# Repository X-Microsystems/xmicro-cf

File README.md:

# XMICRO-CF

[XMICRO](https://github.com/x-microsystems/xmicro-bus) card providing a CompactFlash card interface and real-time
clock.

Datasheet: [XMICRO-CF](Documentation/XMICRO-CF.pdf)

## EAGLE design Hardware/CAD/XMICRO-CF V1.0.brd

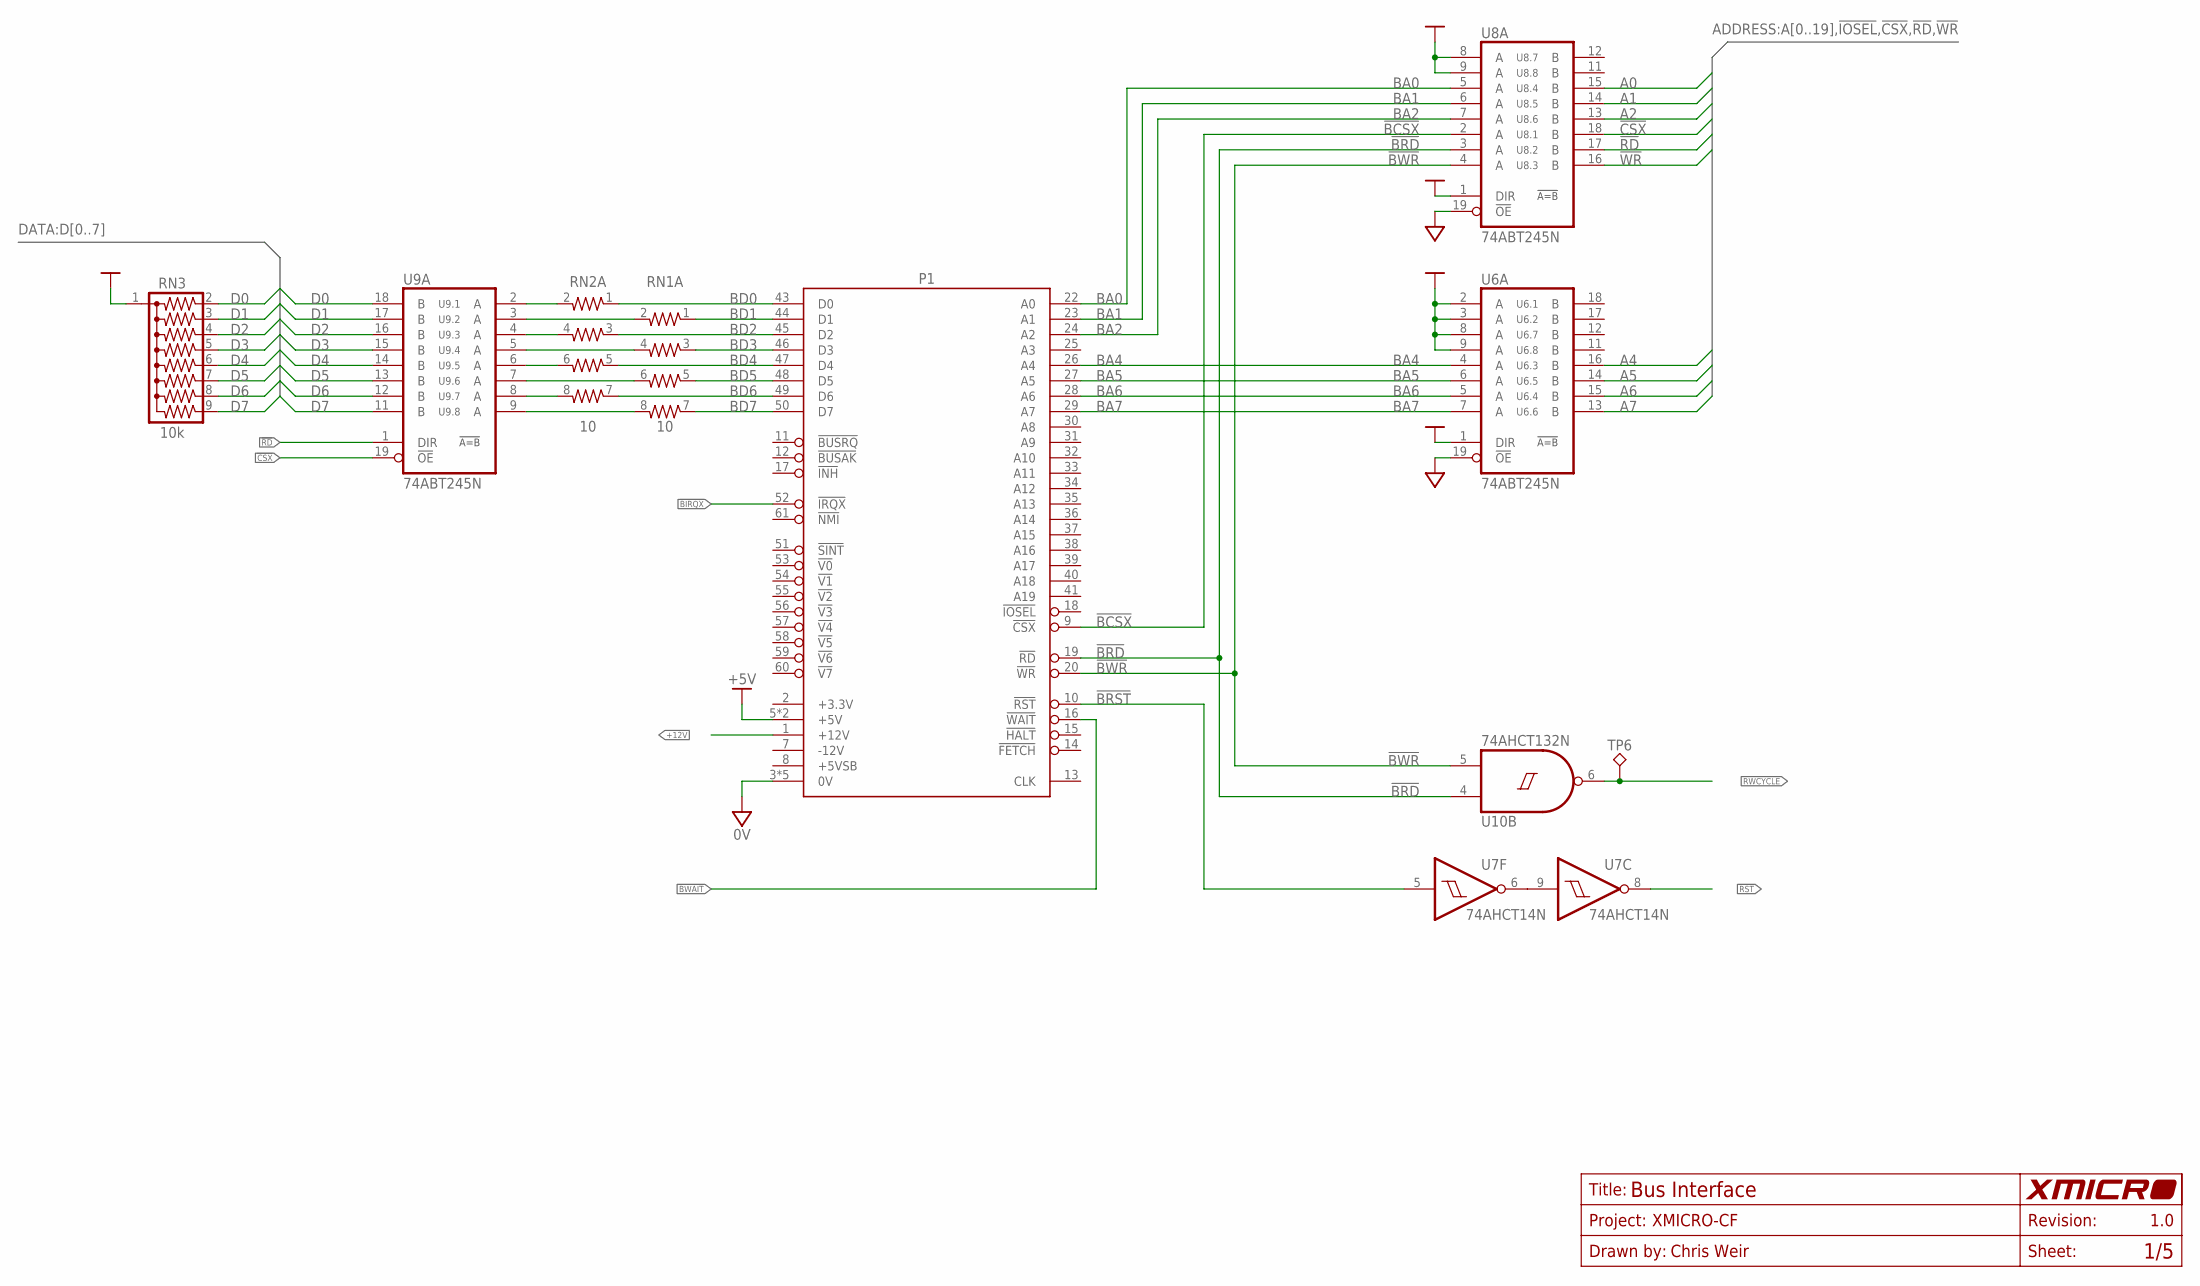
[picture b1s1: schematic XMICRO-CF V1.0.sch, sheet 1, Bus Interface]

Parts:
P1: XMICRO-BUS-EDGE; EDGE62M
RN1, RN2: 10; SIL8
RN3: 10k; SIL9
TP6: TP-040
U6, U8, U9: 74ABT245N; DIL20
U7: 74AHCT14N; DIL14
U10: 74AHCT132N; DIL14

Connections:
0V: P1.3 (0V), P1.4 (0V), P1.21 (0V), P1.42 (0V), P1.62 (0V), U6.10 (0V), U6.19 (!OE), U7.7 (0V), U8.10 (0V), U8.19 (!OE), U9.10 (0V), U10.7 (0V); also elsewhere on the board
!BCSX: P1.9 (!CSX), U8.2 (A)
!BIRQX: P1.52 (!IRQX); also elsewhere on the board
!BRD: P1.19 (!RD), U8.3 (A), U10.4 (I0)
!BRST: P1.10 (!RST), U7.5 (I)
!BWAIT: P1.16 (!WAIT); also elsewhere on the board
!BWR: P1.20 (!WR), U8.4 (A), U10.5 (I1)
!CSX: U8.18 (B), U9.19 (!OE); also elsewhere on the board
!RD: U8.17 (B), U9.1 (DIR); also elsewhere on the board
!RST: U7.8 (O); also elsewhere on the board
!WR: U8.16 (B); also elsewhere on the board
+5V: P1.5 (+5V), P1.6 (+5V), RN3.1, U6.1 (DIR), U6.2 (A), U6.3 (A), U6.8 (A), U6.9 (A), U6.20 (+5V), U7.14 (+5V), U8.1 (DIR), U8.8 (A), U8.9 (A), U8.20 (+5V), U9.20 (+5V), U10.14 (+5V); also elsewhere on the board
+12V: P1.1 (+12V); also elsewhere on the board
A0: U8.15 (B); also elsewhere on the board
A1: U8.14 (B); also elsewhere on the board
A2: U8.13 (B); also elsewhere on the board
A4: U6.16 (B); also elsewhere on the board
A5: U6.14 (B); also elsewhere on the board
A6: U6.15 (B); also elsewhere on the board
A7: U6.13 (B); also elsewhere on the board
BA0: P1.22 (A0), U8.5 (A)
BA1: P1.23 (A1), U8.6 (A)
BA2: P1.24 (A2), U8.7 (A)
BA4: P1.26 (A4), U6.4 (A)
BA5: P1.27 (A5), U6.6 (A)
BA6: P1.28 (A6), U6.5 (A)
BA7: P1.29 (A7), U6.7 (A)
BD0: P1.43 (D0), RN2.1
BD1: P1.44 (D1), RN1.1
BD2: P1.45 (D2), RN2.3 (1)
BD3: P1.46 (D3), RN1.3 (1)
BD4: P1.47 (D4), RN2.5 (1)
BD5: P1.48 (D5), RN1.5 (1)
BD6: P1.49 (D6), RN2.7 (1)
BD7: P1.50 (D7), RN1.7 (1)
D0: RN3.2, U9.18 (B); also elsewhere on the board
D1: RN3.3, U9.17 (B); also elsewhere on the board
D2: RN3.4, U9.16 (B); also elsewhere on the board
D3: RN3.5, U9.15 (B); also elsewhere on the board
D4: RN3.6, U9.14 (B); also elsewhere on the board
D5: RN3.7, U9.13 (B); also elsewhere on the board
D6: RN3.8, U9.12 (B); also elsewhere on the board
D7: RN3.9, U9.11 (B); also elsewhere on the board
unnamed: U7.6 (O), U7.9 (I)
unnamed: RN2.2, U9.2 (A)
unnamed: RN1.2, U9.3 (A)
unnamed: RN2.4 (2), U9.4 (A)
unnamed: RN1.4 (2), U9.5 (A)
unnamed: RN2.6 (2), U9.6 (A)
unnamed: RN1.6 (2), U9.7 (A)
unnamed: RN2.8 (2), U9.8 (A)
unnamed: RN1.8 (2), U9.9 (A)
RWCYCLE: TP6.1, U10.6 (O); also elsewhere on the board

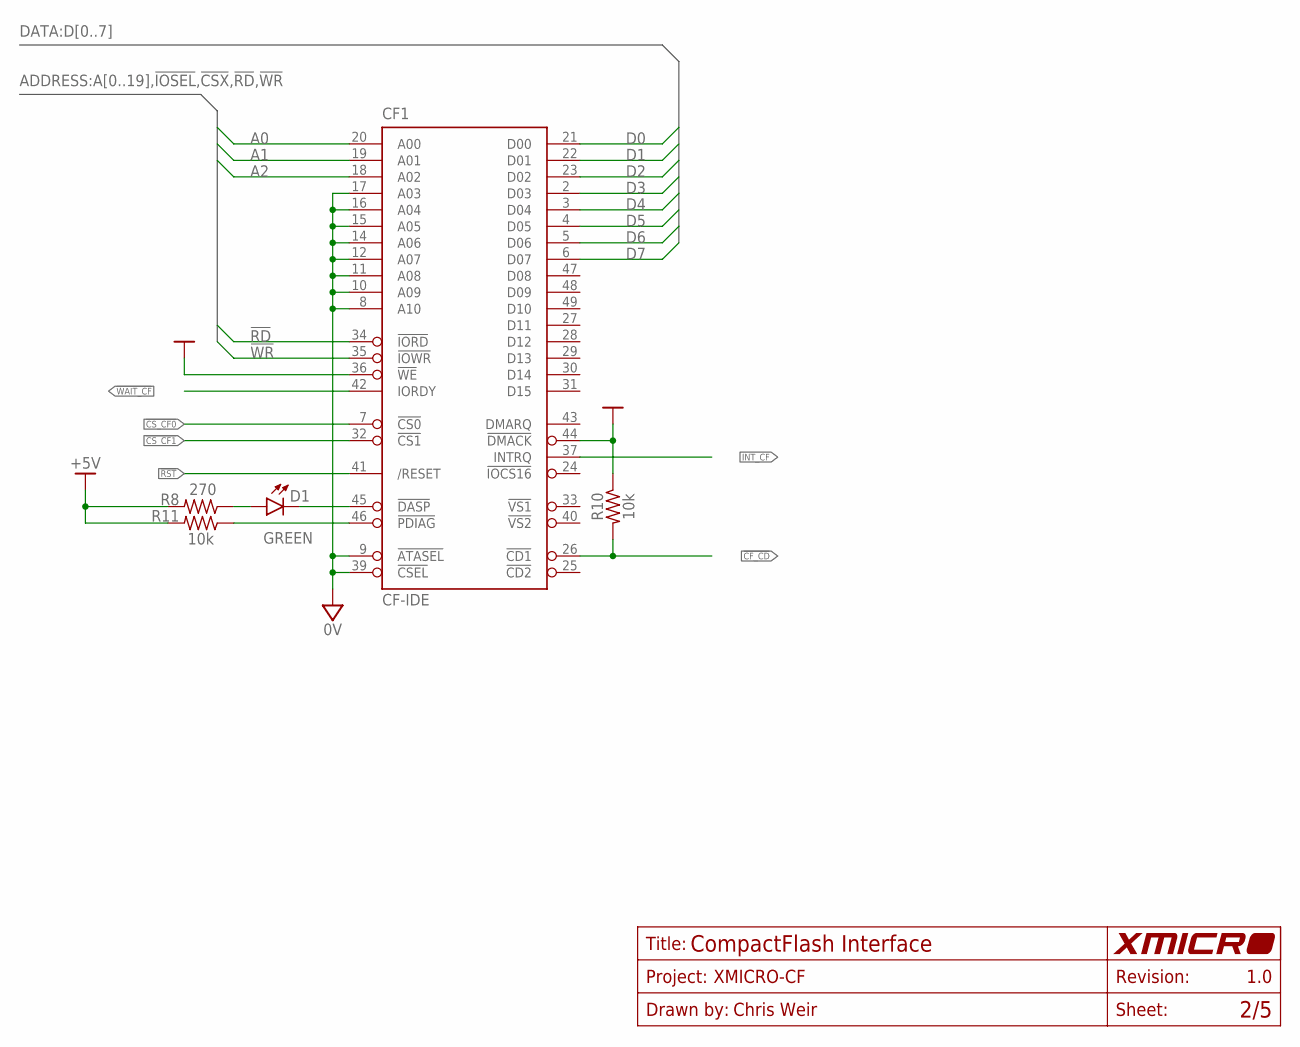
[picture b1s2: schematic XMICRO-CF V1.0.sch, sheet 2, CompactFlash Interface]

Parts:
CF1: CF-IDE; CF-KYOCERA
D1: GREEN; LED-3R
R8: 270; 0207/10
R10, R11: 10k; 0207/10

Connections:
0V: CF1.1 (0V), CF1.8 (A10), CF1.9 (!ATASEL), CF1.10 (A09), CF1.11 (A08), CF1.12 (A07), CF1.14 (A06), CF1.15 (A05), CF1.16 (A04), CF1.17 (A03), CF1.39 (!CSEL), CF1.50 (0V), CF1.M1 (0V), CF1.M2 (0V); also elsewhere on the board
!CF_CD: CF1.26 (!CD1), R10.2; also elsewhere on the board
!CS_CF0: CF1.7 (!CS0); also elsewhere on the board
!CS_CF1: CF1.32 (!CS1); also elsewhere on the board
!RD: CF1.34 (!IORD); also elsewhere on the board
!RST: CF1.41 (/RESET); also elsewhere on the board
!WAIT_CF: CF1.42 (IORDY); also elsewhere on the board
!WR: CF1.35 (!IOWR); also elsewhere on the board
+5V: CF1.13 (+5V), CF1.36 (!WE), CF1.38 (+5V), CF1.44 (!DMACK), R8.2, R10.1, R11.2; also elsewhere on the board
A0: CF1.20 (A00); also elsewhere on the board
A1: CF1.19 (A01); also elsewhere on the board
A2: CF1.18 (A02); also elsewhere on the board
D0: CF1.21 (D00); also elsewhere on the board
D1: CF1.22 (D01); also elsewhere on the board
D2: CF1.23 (D02); also elsewhere on the board
D3: CF1.2 (D03); also elsewhere on the board
D4: CF1.3 (D04); also elsewhere on the board
D5: CF1.4 (D05); also elsewhere on the board
D6: CF1.5 (D06); also elsewhere on the board
D7: CF1.6 (D07); also elsewhere on the board
INT_CF: CF1.37 (INTRQ); also elsewhere on the board
unnamed: CF1.45 (!DASP), D1.C
unnamed: D1.A, R8.1
unnamed: CF1.46 (!PDIAG), R11.1

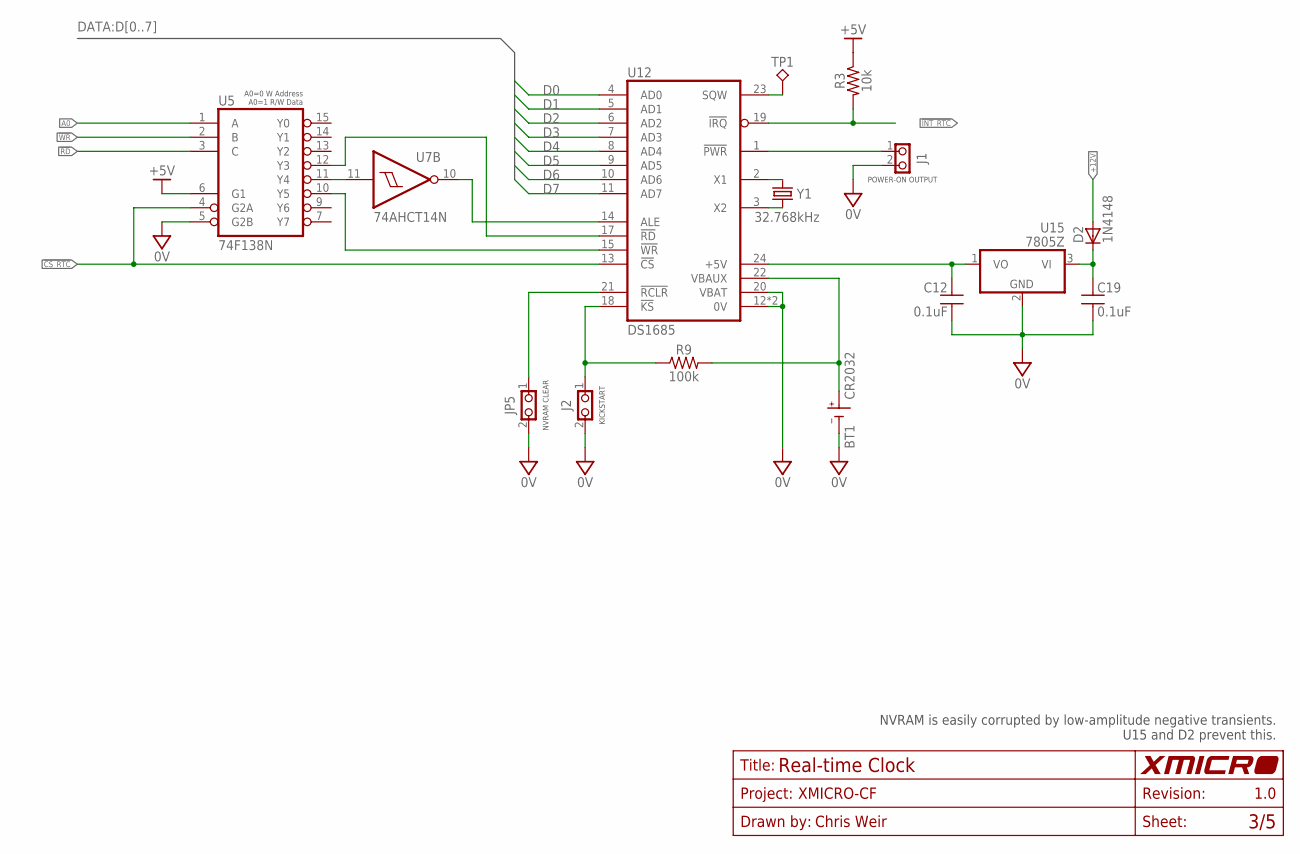
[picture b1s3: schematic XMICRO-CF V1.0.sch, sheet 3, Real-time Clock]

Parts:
BT1: CR2032; BU2032
C12, C19: 0.1uF; C025-024X044
D2: 1N4148; DO35-7
J1: 1X2
J2: 1X2-THRU; 1X2
JP5: 1X2-THRU; 1X2
R3: 10k; 0207/10
R9: 100k; 0207/10
TP1: TP-040
U5: 74F138N; DIL16
U7: 74AHCT14N; DIL14
U12: DS1685; DIL24
U15: 7805Z; TO92
Y1: 32.768kHz; CRYSTAL-3X8N

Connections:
0V: BT1.N (-), C12.2, C19.2, J1.2, J2.2, JP5.2, U5.5 (G2B), U5.8 (0V), U7.7 (0V), U12.12 (0V), U12.16 (0V), U12.20 (VBAT), U15.2 (0V); also elsewhere on the board
!CS_RTC: U5.4 (G2A), U12.13 (!CS); also elsewhere on the board
!INT_RTC: R3.2, U12.19 (!IRQ); also elsewhere on the board
!RD: U5.3 (C); also elsewhere on the board
!WR: U5.2 (B); also elsewhere on the board
+5V: R3.1, U5.6 (G1), U5.16 (+5V), U7.14 (+5V); also elsewhere on the board
+12V: D2.A; also elsewhere on the board
A0: U5.1 (A); also elsewhere on the board
D0: U12.4 (AD0); also elsewhere on the board
D1: U12.5 (AD1); also elsewhere on the board
D2: U12.6 (AD2); also elsewhere on the board
D3: U12.7 (AD3); also elsewhere on the board
D4: U12.8 (AD4); also elsewhere on the board
D5: U12.9 (AD5); also elsewhere on the board
D6: U12.10 (AD6); also elsewhere on the board
D7: U12.11 (AD7); also elsewhere on the board
unnamed: JP5.1, U12.21 (!RCLR)
unnamed: TP1.1, U12.23 (SQW)
unnamed: U12.2 (X1), Y1.2
unnamed: U12.3 (X2), Y1.1
unnamed: U5.10 (Y5), U12.15 (!WR)
unnamed: U5.11 (Y4), U7.11 (I)
unnamed: U5.12 (Y3), U12.17 (!RD)
unnamed: C12.1, U12.24 (+5V), U15.1 (VO)
unnamed: U7.10 (O), U12.14 (ALE)
unnamed: J1.1, U12.1 (!PWR)
unnamed: J2.1, R9.1, U12.18 (!KS)
unnamed: C19.1, D2.C, U15.3 (VI)
unnamed: BT1.P1 (+), BT1.P2 (+), R9.2, U12.22 (VBAUX)

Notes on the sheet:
A0=0 W Address A0=1 R/W Data
NVRAM CLEAR
KICKSTART
POWER-ON OUTPUT
NVRAM is easily corrupted by low-amplitude negative transients. U15 and D2 prevent this.

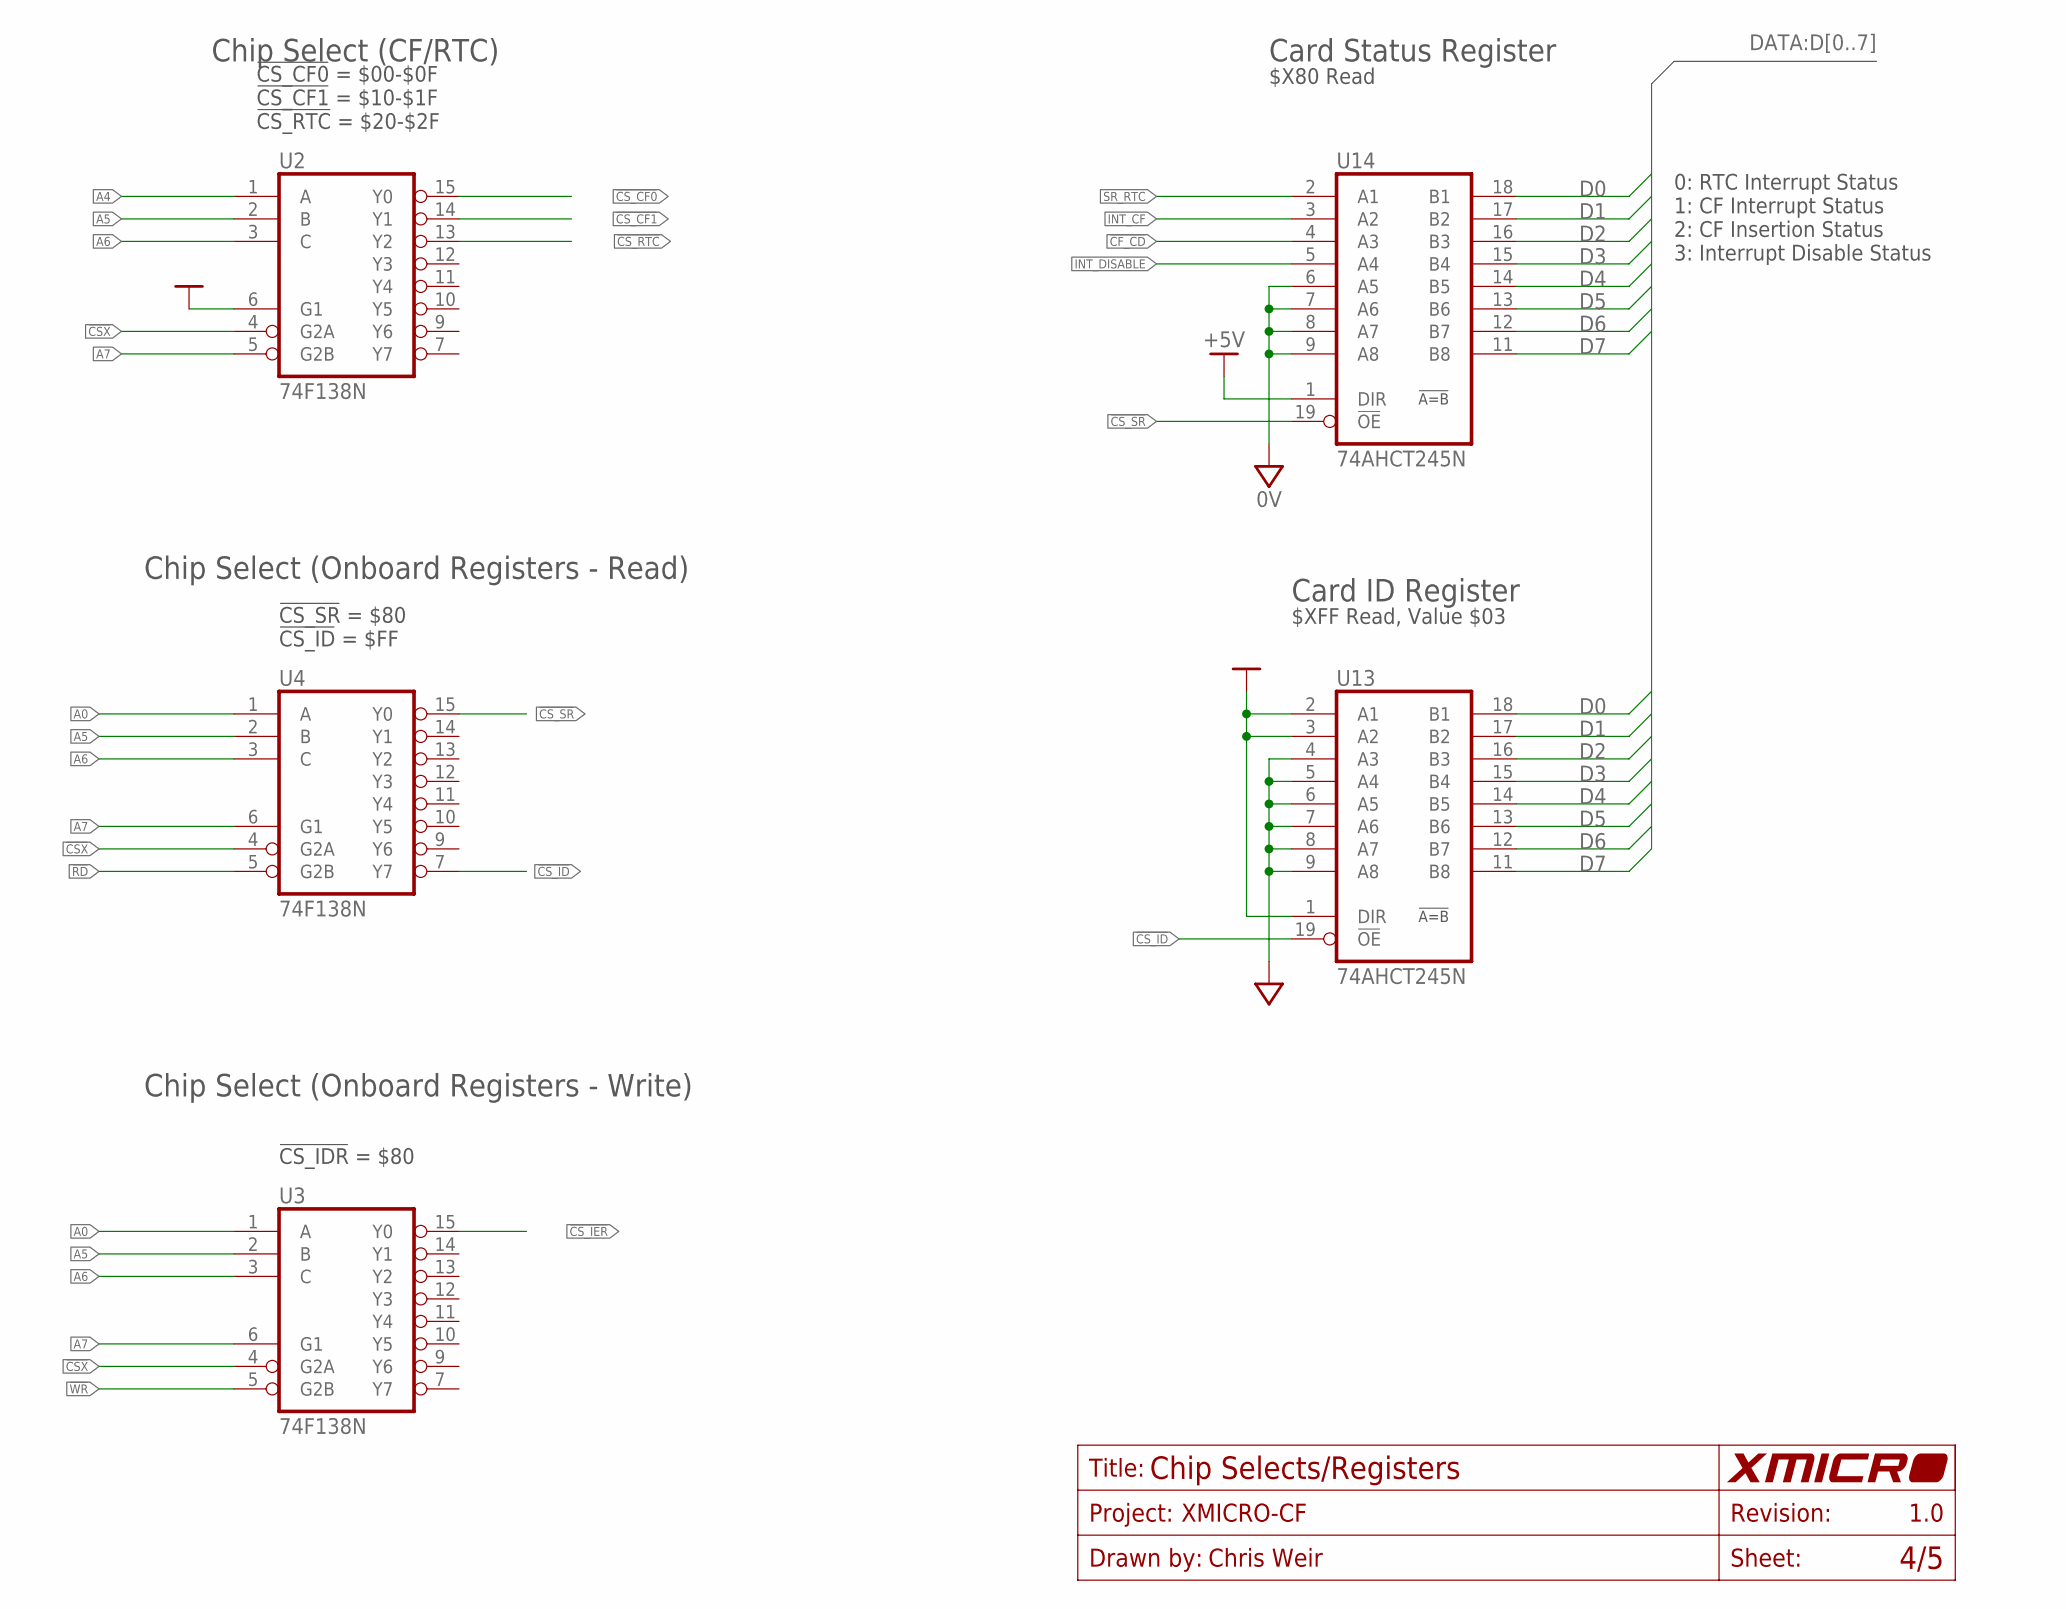
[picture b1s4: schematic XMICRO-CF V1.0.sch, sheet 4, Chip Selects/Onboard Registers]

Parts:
U2, U3, U4: 74F138N; DIL16
U13, U14: 74AHCT245N; DIL20

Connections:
0V: U2.8 (0V), U3.8 (0V), U4.8 (0V), U13.4 (A3), U13.5 (A4), U13.6 (A5), U13.7 (A6), U13.8 (A7), U13.9 (A8), U13.10 (0V), U14.6 (A5), U14.7 (A6), U14.8 (A7), U14.9 (A8), U14.10 (0V); also elsewhere on the board
!CF_CD: U14.4 (A3); also elsewhere on the board
!CSX: U2.4 (G2A), U3.4 (G2A), U4.4 (G2A); also elsewhere on the board
!CS_CF0: U2.15 (Y0); also elsewhere on the board
!CS_CF1: U2.14 (Y1); also elsewhere on the board
!CS_ID: U4.7 (Y7), U13.19 (!OE)
!CS_IER: U3.15 (Y0); also elsewhere on the board
!CS_RTC: U2.13 (Y2); also elsewhere on the board
!CS_SR: U4.15 (Y0), U14.19 (!OE)
!RD: U4.5 (G2B); also elsewhere on the board
!WR: U3.5 (G2B); also elsewhere on the board
+5V: U2.6 (G1), U2.16 (+5V), U3.16 (+5V), U4.16 (+5V), U13.1 (DIR), U13.2 (A1), U13.3 (A2), U13.20 (+5V), U14.1 (DIR), U14.20 (+5V); also elsewhere on the board
A0: U3.1 (A), U4.1 (A); also elsewhere on the board
A4: U2.1 (A); also elsewhere on the board
A5: U2.2 (B), U3.2 (B), U4.2 (B); also elsewhere on the board
A6: U2.3 (C), U3.3 (C), U4.3 (C); also elsewhere on the board
A7: U2.5 (G2B), U3.6 (G1), U4.6 (G1); also elsewhere on the board
D0: U13.18 (B1), U14.18 (B1); also elsewhere on the board
D1: U13.17 (B2), U14.17 (B2); also elsewhere on the board
D2: U13.16 (B3), U14.16 (B3); also elsewhere on the board
D3: U13.15 (B4), U14.15 (B4); also elsewhere on the board
D4: U13.14 (B5), U14.14 (B5); also elsewhere on the board
D5: U13.13 (B6), U14.13 (B6); also elsewhere on the board
D6: U13.12 (B7), U14.12 (B7); also elsewhere on the board
D7: U13.11 (B8), U14.11 (B8); also elsewhere on the board
INT_CF: U14.3 (A2); also elsewhere on the board
INT_DISABLE: U14.5 (A4); also elsewhere on the board
SR_RTC: U14.2 (A1); also elsewhere on the board

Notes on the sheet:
!CS_CF0! = $00-$0F !CS_CF1! = $10-$1F !CS_RTC! = $20-$2F
!CS_SR! = $80 !CS_ID! = $FF
0: RTC Interrupt Status 1: CF Interrupt Status 2: CF Insertion Status 3: Interrupt Disable Status
Chip Select (CF/RTC)
Chip Select (Onboard Registers - Read)
Card Status Register
Card ID Register
$X80 Read
$XFF Read, Value $03
!CS_IDR! = $80
Chip Select (Onboard Registers - Write)

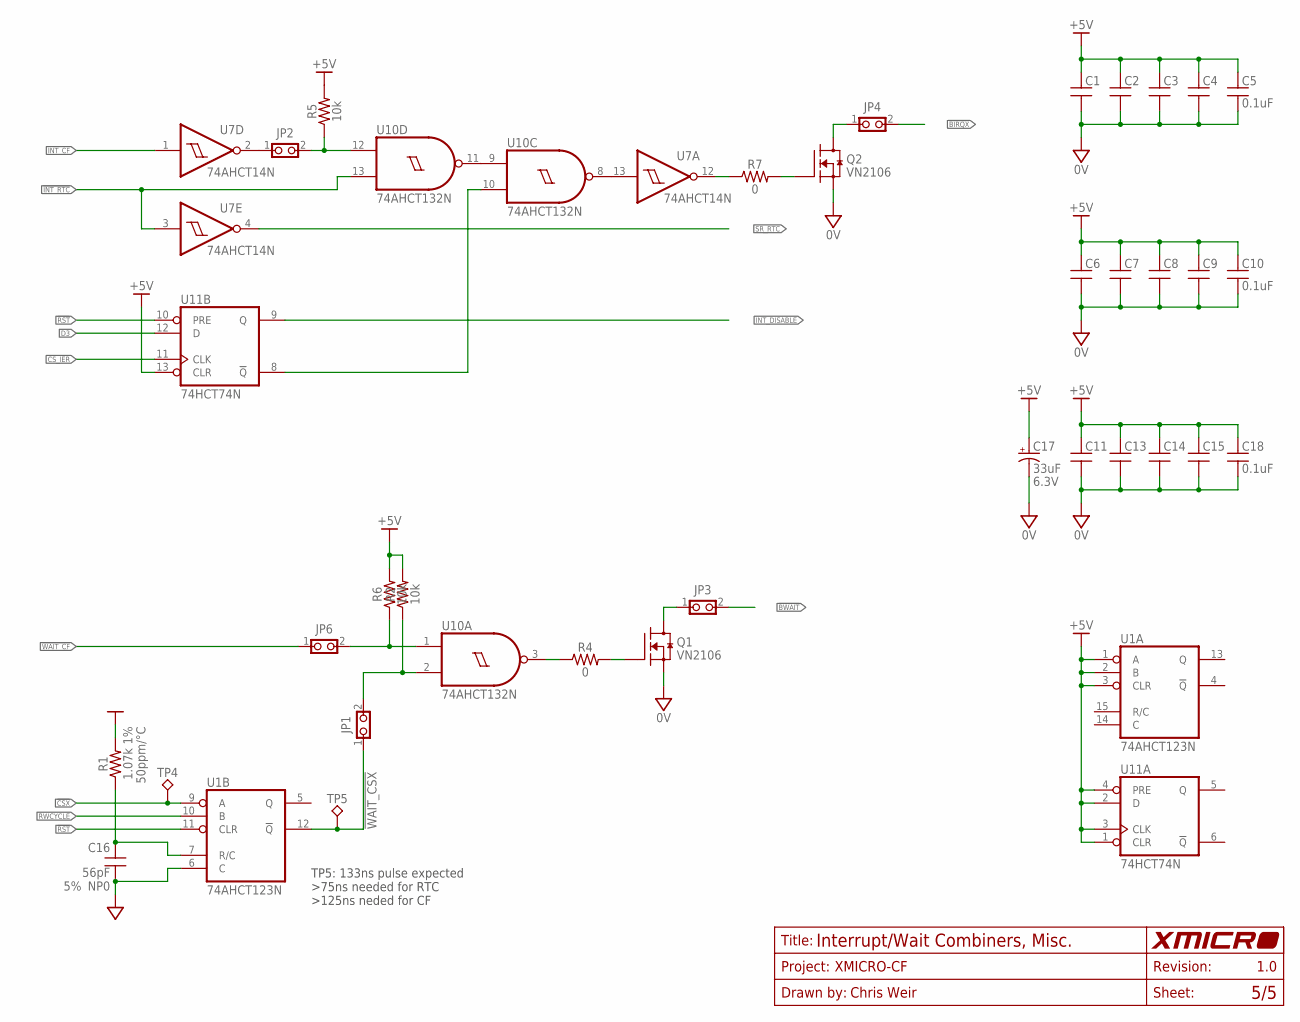
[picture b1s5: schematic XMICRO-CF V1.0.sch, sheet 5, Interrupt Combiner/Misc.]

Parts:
C1, C2, C3, C4, C5, C6, C7, C8, C9, C10, C11, C13, C14, C15, C18: 0.1uF; C025-024X044
C16: 56pF; C025-024X044; TOLERANCE 5%
C17: 33uF; E2,5-6; VOLTAGE 6.3V
JP1, JP2, JP3, JP4, JP6: 1X2-THRU; 1X2
Q1, Q2: VN2106; TO92
R1: 1.07k; 0207/10; TOLERANCE 1%
R2, R5, R6: 10k; 0207/10
R4: 0; 0207/10
R7: 0; 0207/12
TP4, TP5: TP-040
U1: 74AHCT123N; DIL16
U7: 74AHCT14N; DIL14
U10: 74AHCT132N; DIL14
U11: 74HCT74N; DIL14

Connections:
0V: C1.2, C2.2, C3.2, C4.2, C5.2, C6.2, C7.2, C8.2, C9.2, C10.2, C11.2, C13.2, C14.2, C15.2, C16.2, C17.-, C18.2, Q1.1 (S), Q2.1 (S), U1.6 (C), U1.8 (0V), U7.7 (0V), U10.7 (0V), U11.7 (0V); also elsewhere on the board
!BIRQX: JP4.2; also elsewhere on the board
!BWAIT: JP3.2; also elsewhere on the board
!CSX: TP4.1, U1.9 (A); also elsewhere on the board
!CS_IER: U11.11 (CLK); also elsewhere on the board
!INT_RTC: U7.3 (I), U10.13 (I1); also elsewhere on the board
!RST: U1.11 (CLR), U11.10 (PRE); also elsewhere on the board
!WAIT_CF: JP6.1; also elsewhere on the board
!WAIT_CSX: JP1.1, TP5.1, U1.12 (!Q)
+5V: C1.1, C2.1, C3.1, C4.1, C5.1, C6.1, C7.1, C8.1, C9.1, C10.1, C11.1, C13.1, C14.1, C15.1, C17.+, C18.1, R1.2, R2.2, R5.2, R6.2, U1.1 (A), U1.2 (B), U1.3 (CLR), U1.16 (+5V), U7.14 (+5V), U10.14 (+5V), U11.1 (CLR), U11.2 (D), U11.3 (CLK), U11.4 (PRE), U11.13 (CLR), U11.14 (+5V); also elsewhere on the board
D3: U11.12 (D); also elsewhere on the board
INT_CF: U7.1 (I); also elsewhere on the board
INT_DISABLE: U11.9 (Q); also elsewhere on the board
unnamed: U7.13 (I), U10.8 (O)
unnamed: JP2.1, U7.2 (O)
unnamed: Q1.2 (G), R4.2
unnamed: JP3.1, Q1.3 (D)
unnamed: JP6.2, R6.1, U10.1 (I0)
unnamed: Q2.2 (G), R7.2
unnamed: JP4.1, Q2.3 (D)
unnamed: U10.10 (I1), U11.8 (!Q)
unnamed: C16.1, R1.1, U1.7 (R/C)
unnamed: JP1.2, R2.1, U10.2 (I1)
unnamed: U10.9 (I0), U10.11 (O)
unnamed: JP2.2, R5.1, U10.12 (I0)
unnamed: R4.1, U10.3 (O)
unnamed: R7.1, U7.12 (O)
RWCYCLE: U1.10 (B); also elsewhere on the board
SR_RTC: U7.4 (O); also elsewhere on the board

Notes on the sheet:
TP5: 133ns pulse expected >75ns needed for RTC >125ns neded for CF

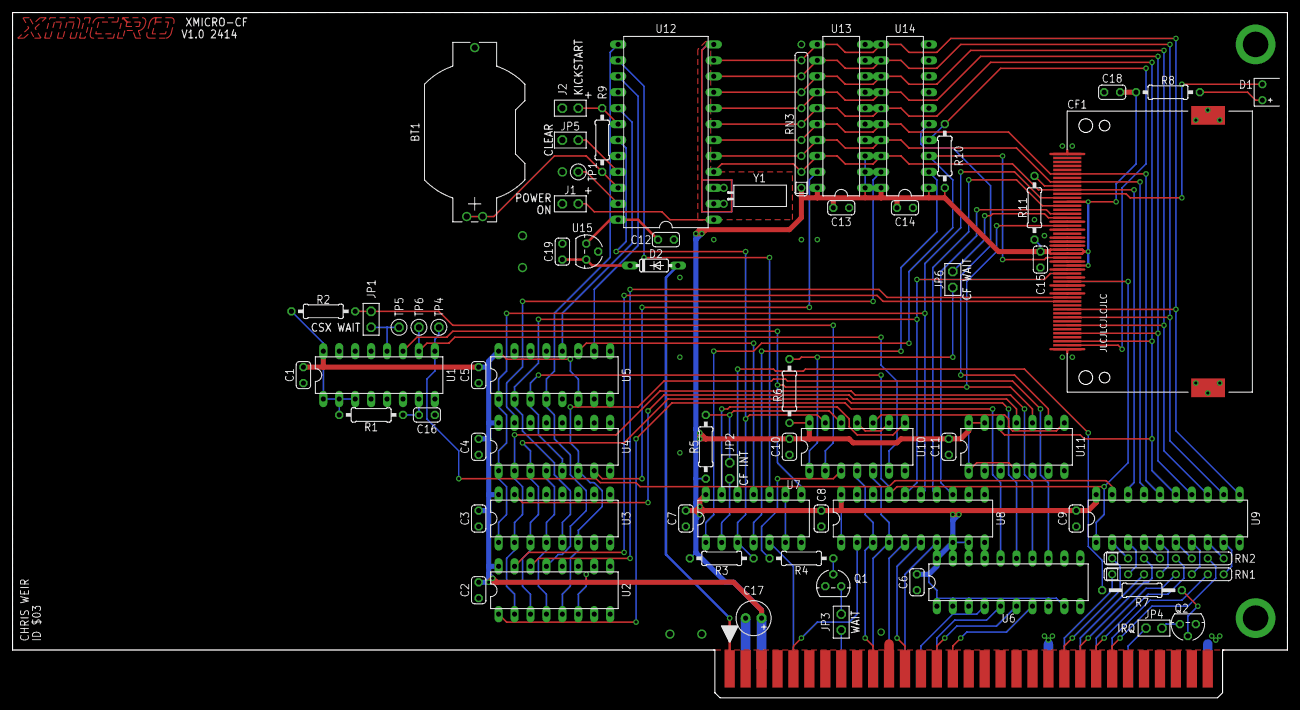
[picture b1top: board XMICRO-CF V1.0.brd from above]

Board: 2 copper layers, 203.2 x 109.2 mm, 68 parts (0 on the bottom side), 96 nets.

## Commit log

2024-09-09 Minor document adjustments
2024-09-15 Rearranged documentation files
2024-09-29 Updated datasheet formatting
2024-09-30 Updated datasheet template
2025-08-05 Updated Readme and photos
2025-12-24 Fixed the Interrupt Disable bit description (wrong polarity)
2026-01-11 Fixed datasheet error (CSR bit-2 polarity)
